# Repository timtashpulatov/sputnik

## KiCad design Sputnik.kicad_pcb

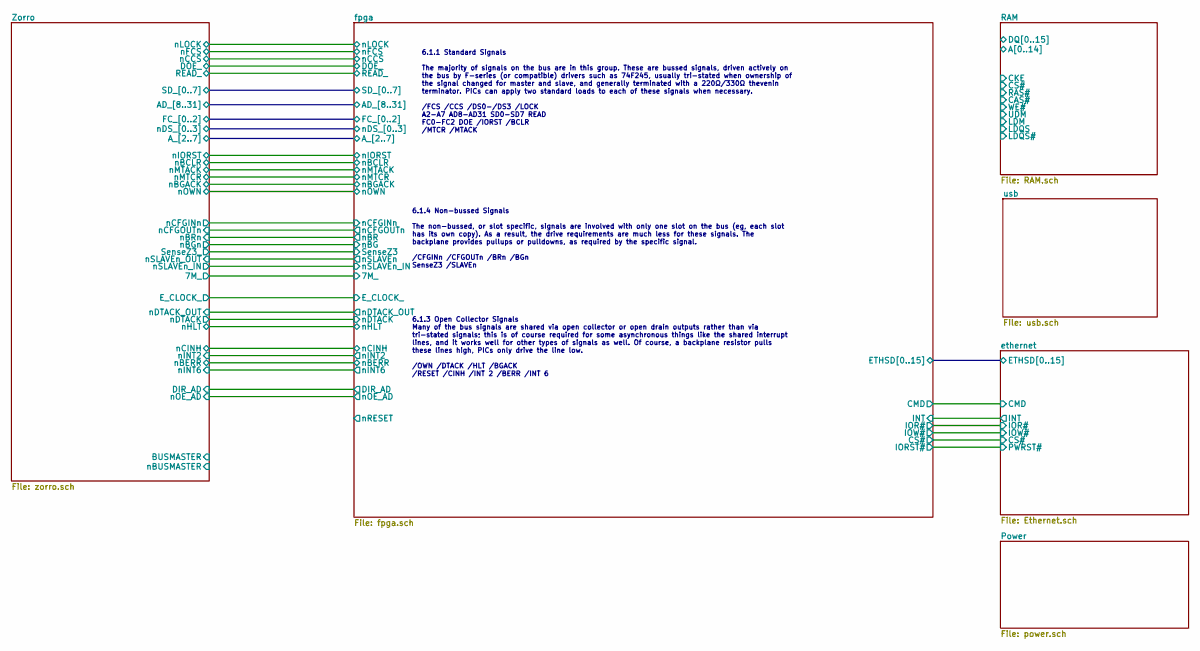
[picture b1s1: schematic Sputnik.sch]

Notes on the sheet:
6.1.1 Standard Signals The majority of signals on the bus are in this group. These are bussed signals, driven actively on the bus by F-series (or compatible) drivers such as 74F245, usually tri-stated when ownership of the signal changed for master and slave, and generally terminated with a 220Ω/33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
6.1.4 Non-bussed Signals The non-bussed, or slot specific, signals are involved with only one slot on the bus (eg, each slot has its own copy). As a result, the drive requirements are much less for these signals. The backplane provides pullups or pulldowns, as required by the specific signal. /CFGI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
6.1.3 Open Collector Signals Many of the bus signals are shared via open collector or open drain outputs rather than via tri-stated signals; this is of course required for some asynchronous things like the shared interrupt lines, and it works well for other types of signals as well. Of course, a ba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

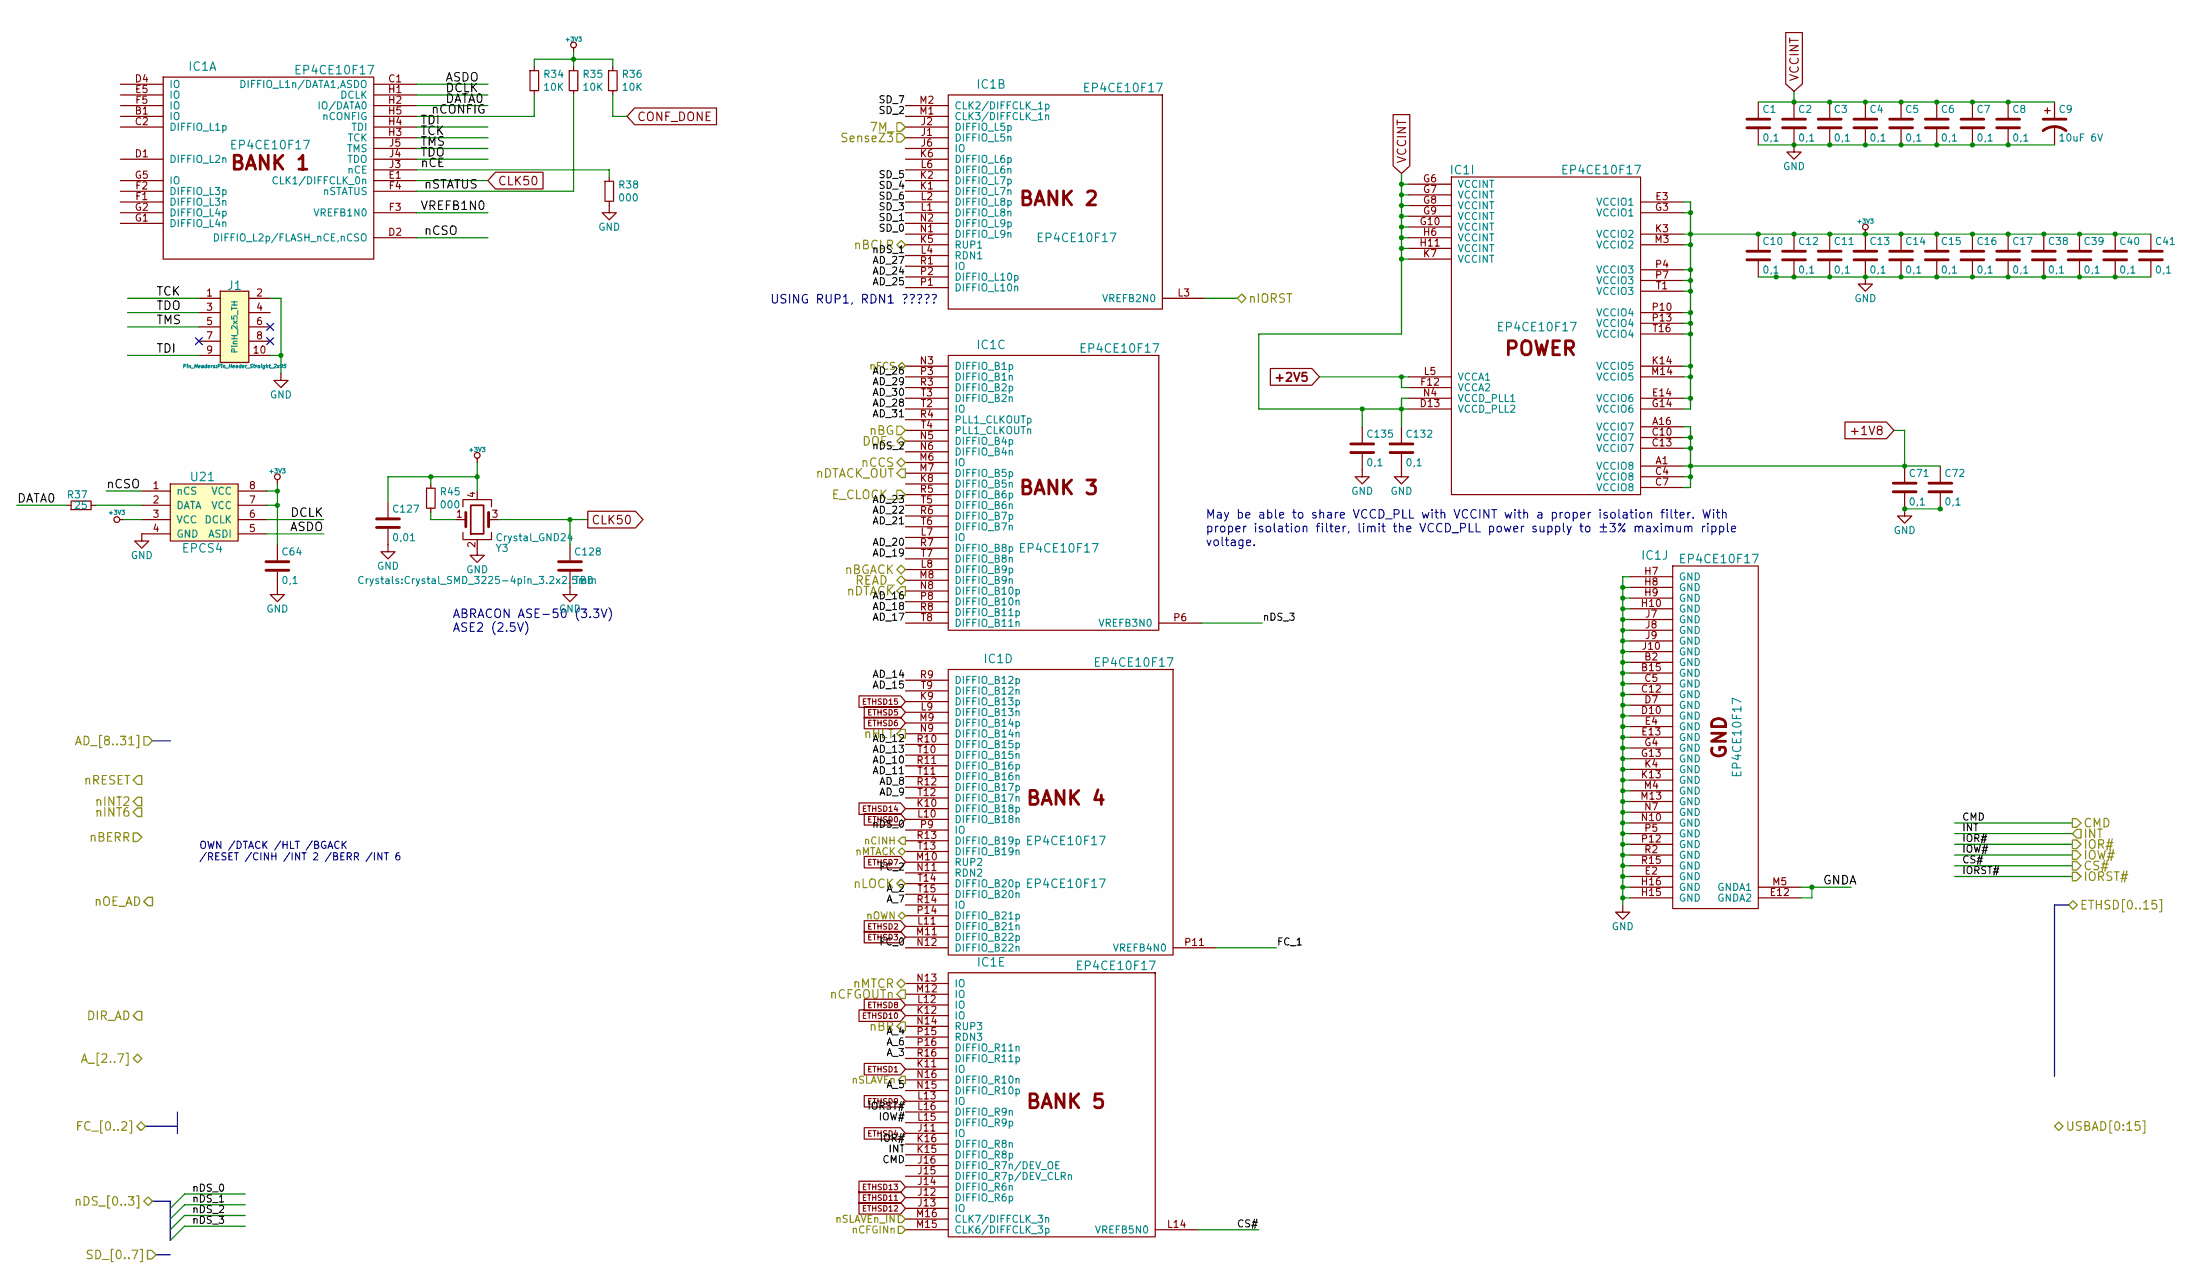
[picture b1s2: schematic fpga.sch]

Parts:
C1, C2, C3, C4, C5, C6, C7, C8, C10, C11, C12, C13, C14, C15, C16, C17, C38, C39, C40, C41, C64, C71, C72: 0,1; C_0603
C9: 10uF 6V
C127: 0,01; C_0603
C128: TBD; C_0603
C132, C135: 0,1; C_0402
IC1: EP4CE10F17; BGA-256-NSMD
J1: Pinheader_2x5_TH_WALL; Pin_Header_Straight_2x05; Manufacturer Part Number SBH11-PBPC-D05-ST-BK
R34, R35, R36: 10K; R_0603
R37: 25; R_0603
R38, R45: 000; R_0603
U21: EPCS4; SOIC-8_3.9x4.9mm_Pitch1.27mm
Y3: Crystal_GND24; Crystal_SMD_3225-4pin_3.2x2.5mm

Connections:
+1V8: C71.1, C72.1, IC1.A1 (VCCIO8), IC1.A16 (VCCIO7), IC1.C4 (VCCIO8), IC1.C7 (VCCIO8), IC1.C10 (VCCIO7), IC1.C13 (VCCIO7); also elsewhere on the board
+2V5: IC1.F12 (VCCA2), IC1.L5 (VCCA1); also elsewhere on the board
+3V3: C10.1, C11.1, C12.1, C13.1, C14.1, C15.1, C16.1, C17.1, C38.1, C39.1, C40.1, C41.1, C64.1, C127.1, IC1.E3 (VCCIO1), IC1.E14 (VCCIO6), IC1.G3 (VCCIO1), IC1.G14 (VCCIO6), IC1.K3 (VCCIO2), IC1.K14 (VCCIO5), IC1.M3 (VCCIO2), IC1.M14 (VCCIO5), IC1.P4 (VCCIO3), IC1.P7 (VCCIO3), IC1.P10 (VCCIO4), IC1.P13 (VCCIO4), IC1.T1 (VCCIO3), IC1.T16 (VCCIO4), R34.1, R35.1, R36.1, R45.1, U21.3 (VCC), U21.7 (VCC), U21.8 (VCC), Y3.4; also elsewhere on the board
/Zorro/7M_: IC1.J2 (DIFFIO_L5p); also elsewhere on the board
/Zorro/AD_8: IC1.R12 (DIFFIO_B17p); also elsewhere on the board
/Zorro/AD_9: IC1.T12 (DIFFIO_B17n); also elsewhere on the board
/Zorro/AD_10: IC1.R11 (DIFFIO_B16p); also elsewhere on the board
/Zorro/AD_11: IC1.T11 (DIFFIO_B16n); also elsewhere on the board
/Zorro/AD_12: IC1.R10 (DIFFIO_B15p); also elsewhere on the board
/Zorro/AD_13: IC1.T10 (DIFFIO_B15n); also elsewhere on the board
/Zorro/AD_14: IC1.R9 (DIFFIO_B12p); also elsewhere on the board
/Zorro/AD_15: IC1.T9 (DIFFIO_B12n); also elsewhere on the board
/Zorro/AD_16: IC1.P8 (DIFFIO_B10n); also elsewhere on the board
/Zorro/AD_17: IC1.T8 (DIFFIO_B11n); also elsewhere on the board
/Zorro/AD_18: IC1.R8 (DIFFIO_B11p); also elsewhere on the board
/Zorro/AD_19: IC1.T7 (DIFFIO_B8n); also elsewhere on the board
/Zorro/AD_20: IC1.R7 (DIFFIO_B8p); also elsewhere on the board
/Zorro/AD_21: IC1.T6 (DIFFIO_B7n); also elsewhere on the board
/Zorro/AD_22: IC1.R6 (DIFFIO_B7p); also elsewhere on the board
/Zorro/AD_23: IC1.T5 (DIFFIO_B6n); also elsewhere on the board
/Zorro/AD_24: IC1.P2 (DIFFIO_L10p); also elsewhere on the board
/Zorro/AD_25: IC1.P1 (DIFFIO_L10n); also elsewhere on the board
/Zorro/AD_26: IC1.P3 (DIFFIO_B1n); also elsewhere on the board
/Zorro/AD_27: IC1.R1 (IO); also elsewhere on the board
/Zorro/AD_28: IC1.T2 (IO); also elsewhere on the board
/Zorro/AD_29: IC1.R3 (DIFFIO_B2p); also elsewhere on the board
/Zorro/AD_30: IC1.T3 (DIFFIO_B2n); also elsewhere on the board
/Zorro/AD_31: IC1.R4 (PLL1_CLKOUTp); also elsewhere on the board
/Zorro/A_2: IC1.T15 (DIFFIO_B20n); also elsewhere on the board
/Zorro/A_3: IC1.R16 (DIFFIO_R11p); also elsewhere on the board
/Zorro/A_4: IC1.P15 (RDN3); also elsewhere on the board
/Zorro/A_5: IC1.N15 (DIFFIO_R10p); also elsewhere on the board
/Zorro/A_6: IC1.P16 (DIFFIO_R11n); also elsewhere on the board
/Zorro/A_7: IC1.R14 (IO); also elsewhere on the board
/Zorro/DOE_: IC1.N5 (DIFFIO_B4p); also elsewhere on the board
/Zorro/E_CLOCK_: IC1.R5 (DIFFIO_B6p); also elsewhere on the board
/Zorro/FC_0: IC1.N12 (DIFFIO_B22n); also elsewhere on the board
/Zorro/FC_1: IC1.P11 (VREFB4N0); also elsewhere on the board
/Zorro/FC_2: IC1.N11 (RDN2); also elsewhere on the board
/Zorro/READ_: IC1.M8 (DIFFIO_B9n); also elsewhere on the board
/Zorro/SD_0: IC1.N1 (DIFFIO_L9n); also elsewhere on the board
/Zorro/SD_1: IC1.N2 (DIFFIO_L9p); also elsewhere on the board
/Zorro/SD_2: IC1.M1 (CLK3/DIFFCLK_1n); also elsewhere on the board
/Zorro/SD_3: IC1.L1 (DIFFIO_L8n); also elsewhere on the board
/Zorro/SD_4: IC1.K1 (DIFFIO_L7n); also elsewhere on the board
/Zorro/SD_5: IC1.K2 (DIFFIO_L7p); also elsewhere on the board
/Zorro/SD_6: IC1.L2 (DIFFIO_L8p); also elsewhere on the board
/Zorro/SD_7: IC1.M2 (CLK2/DIFFCLK_1p); also elsewhere on the board
/Zorro/nBCLR: IC1.K5 (RUP1); also elsewhere on the board
/Zorro/nBGACK: IC1.L8 (DIFFIO_B9p); also elsewhere on the board
/Zorro/nCCS: IC1.M6 (IO); also elsewhere on the board
/Zorro/nCFGINn: IC1.M15 (CLK6/DIFFCLK_3p); also elsewhere on the board
/Zorro/nCFGOUTn: IC1.M12 (IO); also elsewhere on the board
/Zorro/nCINH: IC1.R13 (DIFFIO_B19p); also elsewhere on the board
/Zorro/nDS_0: IC1.P9 (IO); also elsewhere on the board
/Zorro/nDS_1: IC1.L4 (RDN1); also elsewhere on the board
/Zorro/nDS_2: IC1.N6 (DIFFIO_B4n); also elsewhere on the board
/Zorro/nDS_3: IC1.P6 (VREFB3N0); also elsewhere on the board
/Zorro/nDTACK: IC1.N8 (DIFFIO_B10p); also elsewhere on the board
/Zorro/nDTACK_OUT: IC1.M7 (DIFFIO_B5p); also elsewhere on the board
/Zorro/nFCS: IC1.N3 (DIFFIO_B1p); also elsewhere on the board
/Zorro/nHLT: IC1.N9 (DIFFIO_B14n); also elsewhere on the board
/Zorro/nIORST: IC1.L3 (VREFB2N0); also elsewhere on the board
/Zorro/nLOCK: IC1.T14 (DIFFIO_B20p); also elsewhere on the board
/Zorro/nMTACK: IC1.T13 (DIFFIO_B19n); also elsewhere on the board
/Zorro/nMTCR: IC1.N13 (IO); also elsewhere on the board
/Zorro/nOWN: IC1.P14 (DIFFIO_B21p); also elsewhere on the board
/Zorro/nSLAVEn_IN: IC1.M16 (CLK7/DIFFCLK_3n); also elsewhere on the board
/ethernet/CMD: IC1.J16 (DIFFIO_R7n/DEV_OE); also elsewhere on the board
/ethernet/CS#: IC1.L14 (VREFB5N0); also elsewhere on the board
/ethernet/INT: IC1.K15 (DIFFIO_R8p); also elsewhere on the board
/ethernet/IOR#: IC1.K16 (DIFFIO_R8n); also elsewhere on the board
/ethernet/IOW#: IC1.L15 (DIFFIO_R9p); also elsewhere on the board
/fpga/ASDO: IC1.C1 (DIFFIO_L1n/DATA1,ASDO), U21.5 (ASDI)
/fpga/DATA0: IC1.H2 (IO/DATA0), R37.1
/fpga/DCLK: IC1.H1 (DCLK), U21.6 (DCLK)
/fpga/IORST#: IC1.L16 (DIFFIO_R9n); also elsewhere on the board
/fpga/SenseZ3: IC1.J1 (DIFFIO_L5n); also elsewhere on the board
/fpga/TCK: IC1.H3 (TCK), J1.1
/fpga/TDI: IC1.H4 (TDI), J1.9
/fpga/TDO: IC1.J4 (TDO), J1.3
/fpga/TMS: IC1.J5 (TMS), J1.5
/fpga/VREFB1N0: IC1.F3 (VREFB1N0)
/fpga/nBG: IC1.T4 (PLL1_CLKOUTn); also elsewhere on the board
/fpga/nBR: IC1.N14 (RUP3); also elsewhere on the board
/fpga/nCE: IC1.J3 (nCE), R38.1
/fpga/nCONFIG: IC1.H5 (nCONFIG), R34.2
/fpga/nCSO: IC1.D2 (DIFFIO_L2p/FLASH_nCE,nCSO), U21.1 (nCS)
/fpga/nSLAVEn: IC1.N16 (DIFFIO_R10n); also elsewhere on the board
/fpga/nSTATUS: IC1.F4 (nSTATUS), R35.2
CLK50: C128.1, IC1.E1 (CLK1/DIFFCLK_0n), Y3.3
CONF_DONE: R36.2; also elsewhere on the board
ETHSD0: IC1.L10 (DIFFIO_B18n); also elsewhere on the board
ETHSD1: IC1.K11 (IO); also elsewhere on the board
ETHSD2: IC1.L11 (DIFFIO_B21n); also elsewhere on the board
ETHSD3: IC1.M11 (DIFFIO_B22p); also elsewhere on the board
ETHSD4: IC1.J11 (IO); also elsewhere on the board
ETHSD5: IC1.L9 (DIFFIO_B13n); also elsewhere on the board
ETHSD6: IC1.M9 (DIFFIO_B14p); also elsewhere on the board
ETHSD7: IC1.M10 (RUP2); also elsewhere on the board
ETHSD8: IC1.L12 (IO); also elsewhere on the board
ETHSD9: IC1.L13 (IO); also elsewhere on the board
ETHSD10: IC1.K12 (IO); also elsewhere on the board
ETHSD11: IC1.J12 (DIFFIO_R6p); also elsewhere on the board
ETHSD12: IC1.J13 (IO); also elsewhere on the board
ETHSD13: IC1.J14 (DIFFIO_R6n); also elsewhere on the board
ETHSD14: IC1.K10 (DIFFIO_B18p); also elsewhere on the board
ETHSD15: IC1.K9 (DIFFIO_B13p); also elsewhere on the board
GND: C1.2, C2.2, C3.2, C4.2, C5.2, C6.2, C7.2, C8.2, C9.2, C10.2, C11.2, C12.2, C13.2, C14.2, C15.2, C16.2, C17.2, C38.2, C39.2, C40.2, C41.2, C64.2, C71.2, C72.2, C127.2, C128.2, C132.2, C135.2, IC1.B2 (GND), IC1.B15 (GND), IC1.C5 (GND), IC1.C12 (GND), IC1.D7 (GND), IC1.D10 (GND), IC1.E2 (GND), IC1.E4 (GND), IC1.E12 (GNDA2), IC1.E13 (GND), IC1.G4 (GND), IC1.G13 (GND), IC1.H7 (GND), IC1.H8 (GND), IC1.H9 (GND), IC1.H10 (GND), IC1.H15 (GND), IC1.H16 (GND), IC1.J7 (GND), IC1.J8 (GND), IC1.J9 (GND), IC1.J10 (GND), IC1.K4 (GND), IC1.K13 (GND), IC1.M4 (GND), IC1.M5 (GNDA1), IC1.M13 (GND), IC1.N7 (GND), IC1.N10 (GND), IC1.P5 (GND), IC1.P12 (GND), IC1.R2 (GND), IC1.R15 (GND), J1.2, J1.10, R38.2, U21.4 (GND), Y3.2; also elsewhere on the board
unnamed: R37.2, U21.2 (DATA)
unnamed: R45.2, Y3.1
VCCINT: C1.1, C2.1, C3.1, C4.1, C5.1, C6.1, C7.1, C8.1, C9.1, C132.1, C135.1, IC1.D13 (VCCD_PLL2), IC1.G6 (VCCINT), IC1.G7 (VCCINT), IC1.G8 (VCCINT), IC1.G9 (VCCINT), IC1.G10 (VCCINT), IC1.H6 (VCCINT), IC1.H11 (VCCINT), IC1.K7 (VCCINT), IC1.N4 (VCCD_PLL1); also elsewhere on the board

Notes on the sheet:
OWN /DTACK /HLT /BGACK /RESET /CINH /INT 2 /BERR /INT 6
USING RUP1, RDN1 ?????
ABRACON ASE-50 (3.3V) ASE2 (2.5V)
May be able to share VCCD_PLL with VCCINT with a proper isolation filter. With proper isolation filter, limit the VCCD_PLL power supply to ±3% maximum ripple voltage.

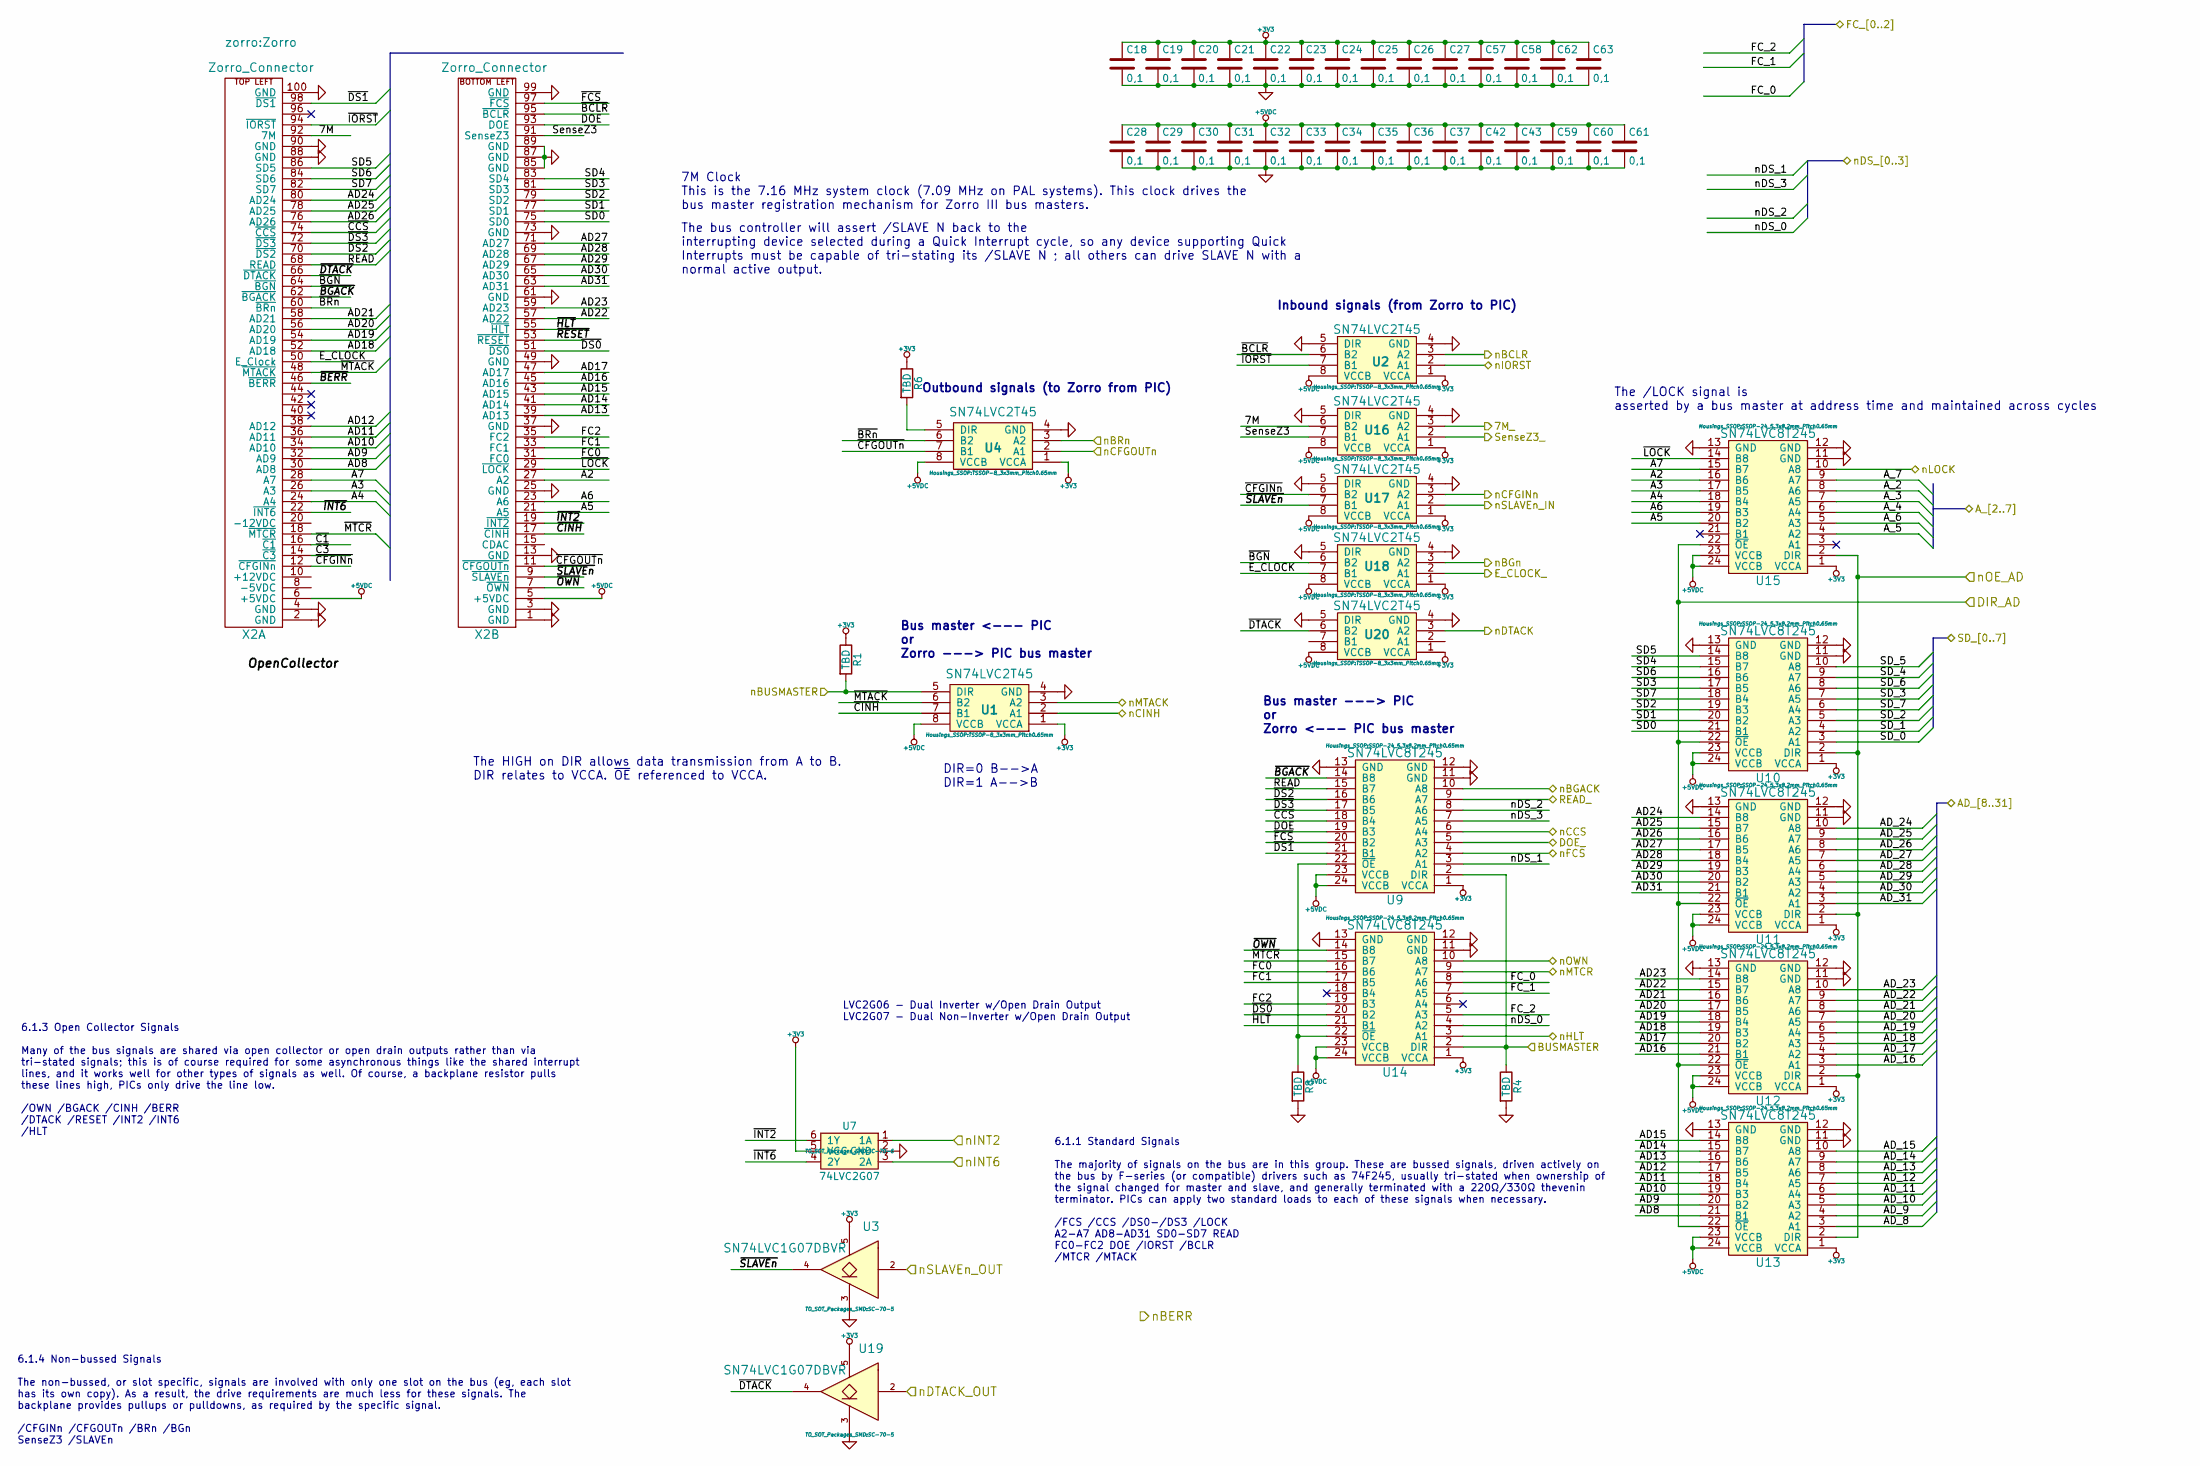
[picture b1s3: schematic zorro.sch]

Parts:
C18, C19, C20, C21, C22, C23, C24, C25, C26, C27, C28, C29, C30, C31, C32, C33, C34, C35, C36, C37, C42, C43, C57, C58, C59, C60, C61, C62, C63: 0,1; C_0603
R1, R4, R6, R8: TBD; R_0603
U1, U2, U4, U16, U17, U18, U20: SN74LVC2T45; TSSOP-8_3x3mm_Pitch0.65mm
U3, U19: SN74LVC1G07DCK; SC-70-5
U7: 74LVC2G07; SC-70-6
U9, U10, U11, U12, U13, U14, U15: SN74LVC8T245; SSOP-24_5.3x8.2mm_Pitch0.65mm
X2: Zorro_Connector; Zorro

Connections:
+3V3: C18.1, C19.1, C20.1, C21.1, C22.1, C23.1, C24.1, C25.1, C26.1, C27.1, C57.1, C58.1, C62.1, C63.1, R1.1, R6.1, U1.1 (VCCA), U2.1 (VCCA), U3.5, U4.1 (VCCA), U7.5 (VCC), U9.1 (VCCA), U10.1 (VCCA), U11.1 (VCCA), U12.1 (VCCA), U13.1 (VCCA), U14.1 (VCCA), U15.1 (VCCA), U16.1 (VCCA), U17.1 (VCCA), U18.1 (VCCA), U19.5, U20.1 (VCCA); also elsewhere on the board
+5VDC: C28.1, C29.1, C30.1, C31.1, C32.1, C33.1, C34.1, C35.1, C36.1, C37.1, C42.1, C43.1, C59.1, C60.1, C61.1, U1.8 (VCCB), U2.8 (VCCB), U4.8 (VCCB), U9.23 (VCCB), U9.24 (VCCB), U10.23 (VCCB), U10.24 (VCCB), U11.23 (VCCB), U11.24 (VCCB), U12.23 (VCCB), U12.24 (VCCB), U13.23 (VCCB), U13.24 (VCCB), U14.23 (VCCB), U14.24 (VCCB), U15.23 (VCCB), U15.24 (VCCB), U16.8 (VCCB), U17.8 (VCCB), U18.8 (VCCB), U20.8 (VCCB), X2.5 (+5VDC), X2.6 (+5VDC); also elsewhere on the board
/Zorro/7M: U16.6 (B2), X2.92 (7M)
/Zorro/7M_: U16.3 (A2); also elsewhere on the board
/Zorro/A2: U15.16 (B6), X2.27 (A2)
/Zorro/A3: U15.17 (B5), X2.26 (A3)
/Zorro/A4: U15.18 (B4), X2.24 (A4)
/Zorro/A5: U15.20 (B2), X2.21 (A5)
/Zorro/A6: U15.19 (B3), X2.23 (A6)
/Zorro/A7: U15.15 (B7), X2.28 (A7)
/Zorro/AD8: U13.21 (B1), X2.30 (AD8)
/Zorro/AD9: U13.20 (B2), X2.32 (AD9)
/Zorro/AD10: U13.19 (B3), X2.34 (AD10)
/Zorro/AD11: U13.18 (B4), X2.36 (AD11)
/Zorro/AD12: U13.17 (B5), X2.38 (AD12)
/Zorro/AD13: U13.16 (B6), X2.39 (AD13)
/Zorro/AD14: U13.15 (B7), X2.41 (AD14)
/Zorro/AD15: U13.14 (B8), X2.43 (AD15)
/Zorro/AD16: U12.21 (B1), X2.45 (AD16)
/Zorro/AD17: U12.20 (B2), X2.47 (AD17)
/Zorro/AD18: U12.19 (B3), X2.52 (AD18)
/Zorro/AD19: U12.18 (B4), X2.54 (AD19)
/Zorro/AD20: U12.17 (B5), X2.56 (AD20)
/Zorro/AD21: U12.16 (B6), X2.58 (AD21)
/Zorro/AD22: U12.15 (B7), X2.57 (AD22)
/Zorro/AD23: U12.14 (B8), X2.59 (AD23)
/Zorro/AD24: U11.14 (B8), X2.80 (AD24)
/Zorro/AD25: U11.15 (B7), X2.78 (AD25)
/Zorro/AD26: U11.16 (B6), X2.76 (AD26)
/Zorro/AD27: U11.17 (B5), X2.71 (AD27)
/Zorro/AD28: U11.18 (B4), X2.69 (AD28)
/Zorro/AD29: U11.19 (B3), X2.67 (AD29)
/Zorro/AD30: U11.20 (B2), X2.65 (AD30)
/Zorro/AD31: U11.21 (B1), X2.63 (AD31)
/Zorro/AD_8: U13.3 (A1); also elsewhere on the board
/Zorro/AD_9: U13.4 (A2); also elsewhere on the board
/Zorro/AD_10: U13.5 (A3); also elsewhere on the board
/Zorro/AD_11: U13.6 (A4); also elsewhere on the board
/Zorro/AD_12: U13.7 (A5); also elsewhere on the board
/Zorro/AD_13: U13.8 (A6); also elsewhere on the board
/Zorro/AD_14: U13.9 (A7); also elsewhere on the board
/Zorro/AD_15: U13.10 (A8); also elsewhere on the board
/Zorro/AD_16: U12.3 (A1); also elsewhere on the board
/Zorro/AD_17: U12.4 (A2); also elsewhere on the board
/Zorro/AD_18: U12.5 (A3); also elsewhere on the board
/Zorro/AD_19: U12.6 (A4); also elsewhere on the board
/Zorro/AD_20: U12.7 (A5); also elsewhere on the board
/Zorro/AD_21: U12.8 (A6); also elsewhere on the board
/Zorro/AD_22: U12.9 (A7); also elsewhere on the board
/Zorro/AD_23: U12.10 (A8); also elsewhere on the board
/Zorro/AD_24: U11.10 (A8); also elsewhere on the board
/Zorro/AD_25: U11.9 (A7); also elsewhere on the board
/Zorro/AD_26: U11.8 (A6); also elsewhere on the board
/Zorro/AD_27: U11.7 (A5); also elsewhere on the board
/Zorro/AD_28: U11.6 (A4); also elsewhere on the board
/Zorro/AD_29: U11.5 (A3); also elsewhere on the board
/Zorro/AD_30: U11.4 (A2); also elsewhere on the board
/Zorro/AD_31: U11.3 (A1); also elsewhere on the board
/Zorro/A_2: U15.8 (A6); also elsewhere on the board
/Zorro/A_3: U15.7 (A5); also elsewhere on the board
/Zorro/A_4: U15.6 (A4); also elsewhere on the board
/Zorro/A_5: U15.4 (A2); also elsewhere on the board
/Zorro/A_6: U15.5 (A3); also elsewhere on the board
/Zorro/A_7: U15.9 (A7); also elsewhere on the board
/Zorro/BUSMASTER: R4.1, U9.2 (DIR), U14.2 (DIR)
/Zorro/DIR_AD: U10.22 (~OE), U11.22 (~OE), U12.22 (~OE), U13.22 (~OE), U15.22 (~OE)
/Zorro/DOE: U9.19 (B3), X2.93 (DOE)
/Zorro/DOE_: U9.5 (A3); also elsewhere on the board
/Zorro/E_CLOCK: U18.7 (B1), X2.50 (E_Clock)
/Zorro/E_CLOCK_: U18.2 (A1); also elsewhere on the board
/Zorro/FC0: U14.16 (B6), X2.31 (FC0)
/Zorro/FC1: U14.17 (B5), X2.33 (FC1)
/Zorro/FC2: U14.19 (B3), X2.35 (FC2)
/Zorro/FC_0: U14.8 (A6); also elsewhere on the board
/Zorro/FC_1: U14.7 (A5); also elsewhere on the board
/Zorro/FC_2: U14.5 (A3); also elsewhere on the board
/Zorro/READ: U9.15 (B7), X2.68 (READ)
/Zorro/READ_: U9.9 (A7); also elsewhere on the board
/Zorro/SD0: U10.21 (B1), X2.75 (SD0)
/Zorro/SD1: U10.20 (B2), X2.77 (SD1)
/Zorro/SD2: U10.19 (B3), X2.79 (SD2)
/Zorro/SD3: U10.17 (B5), X2.81 (SD3)
/Zorro/SD4: U10.15 (B7), X2.83 (SD4)
/Zorro/SD5: U10.14 (B8), X2.86 (SD5)
/Zorro/SD6: U10.16 (B6), X2.84 (SD6)
/Zorro/SD7: U10.18 (B4), X2.82 (SD7)
/Zorro/SD_0: U10.3 (A1); also elsewhere on the board
/Zorro/SD_1: U10.4 (A2); also elsewhere on the board
/Zorro/SD_2: U10.5 (A3); also elsewhere on the board
/Zorro/SD_3: U10.7 (A5); also elsewhere on the board
/Zorro/SD_4: U10.9 (A7); also elsewhere on the board
/Zorro/SD_5: U10.10 (A8); also elsewhere on the board
/Zorro/SD_6: U10.8 (A6); also elsewhere on the board
/Zorro/SD_7: U10.6 (A4); also elsewhere on the board
/Zorro/SenseZ3: U16.7 (B1), X2.91 (SenseZ3)
/Zorro/nBCLR: U2.3 (A2); also elsewhere on the board
/Zorro/nBGACK: U9.10 (A8); also elsewhere on the board
/Zorro/nBUSMASTER: R1.2, U1.5 (DIR)
/Zorro/nCCS: U9.6 (A4); also elsewhere on the board
/Zorro/nCFGINn: U17.3 (A2); also elsewhere on the board
/Zorro/nCFGOUTn: U4.2 (A1); also elsewhere on the board
/Zorro/nCINH: U1.2 (A1); also elsewhere on the board
/Zorro/nDS_0: U14.4 (A2); also elsewhere on the board
/Zorro/nDS_1: U9.3 (A1); also elsewhere on the board
/Zorro/nDS_2: U9.8 (A6); also elsewhere on the board
/Zorro/nDS_3: U9.7 (A5); also elsewhere on the board
/Zorro/nDTACK: U20.3 (A2); also elsewhere on the board
/Zorro/nDTACK_OUT: U19.2; also elsewhere on the board
/Zorro/nFCS: U9.4 (A2); also elsewhere on the board
/Zorro/nHLT: U14.3 (A1); also elsewhere on the board
/Zorro/nINT2: U7.1 (1A)
/Zorro/nINT6: U7.3 (2A)
/Zorro/nIORST: U2.2 (A1); also elsewhere on the board
/Zorro/nLOCK: U15.10 (A8); also elsewhere on the board
/Zorro/nMTACK: U1.3 (A2); also elsewhere on the board
/Zorro/nMTCR: U14.9 (A7); also elsewhere on the board
/Zorro/nOE_AD: U10.2 (DIR), U11.2 (DIR), U12.2 (DIR), U13.2 (DIR), U15.2 (DIR)
/Zorro/nOWN: U14.10 (A8); also elsewhere on the board
/Zorro/nSLAVEn_IN: U17.2 (A1); also elsewhere on the board
/Zorro/~BCLR: U2.6 (B2), X2.95 (~BCLR)
/Zorro/~BERR: X2.46 (~BERR)
/Zorro/~BGACK: U9.14 (B8), X2.62 (~BGACK)
/Zorro/~BGN: U18.6 (B2), X2.64 (~BGN)
/Zorro/~BRn: U4.6 (B2), X2.60 (~BRn)
/Zorro/~C1: X2.16 (~C1)
/Zorro/~C3: X2.14 (~C3)
/Zorro/~CCS: U9.18 (B4), X2.74 (~CCS)
/Zorro/~CFGINn: U17.6 (B2), X2.12 (~CFGINn)
/Zorro/~CFGOUTn: U4.7 (B1), X2.11 (~CFGOUTn)
/Zorro/~CINH: U1.7 (B1), X2.17 (~CINH)
/Zorro/~DS0: U14.20 (B2), X2.51 (~DS0)
/Zorro/~DS1: U9.21 (B1), X2.98 (~DS1)
/Zorro/~DS2: U9.16 (B6), X2.70 (~DS2)
/Zorro/~DS3: U9.17 (B5), X2.72 (~DS3)
/Zorro/~DTACK: U19.4, U20.6 (B2), X2.66 (~DTACK)
/Zorro/~FCS: U9.20 (B2), X2.97 (~FCS)
/Zorro/~HLT: U14.21 (B1), X2.55 (~HLT)
/Zorro/~INT2: U7.6 (1Y), X2.19 (~INT2)
/Zorro/~INT6: U7.4 (2Y), X2.22 (~INT6)
/Zorro/~IORST: U2.7 (B1), X2.94 (~IORST)
/Zorro/~LOCK: U15.14 (B8), X2.29 (~LOCK)
/Zorro/~MTACK: U1.6 (B2), X2.48 (~MTACK)
/Zorro/~MTCR: U14.15 (B7), X2.18 (~MTCR)
/Zorro/~OWN: U14.14 (B8), X2.7 (~OWN)
/Zorro/~RESET: X2.53 (~RESET)
/Zorro/~SLAVEn: U3.4, U17.7 (B1), X2.9 (~SLAVEn)
/fpga/SenseZ3: U16.2 (A1); also elsewhere on the board
/fpga/nBG: U18.3 (A2); also elsewhere on the board
/fpga/nBR: U4.3 (A2); also elsewhere on the board
/fpga/nSLAVEn: U3.2; also elsewhere on the board
GND: C18.2, C19.2, C20.2, C21.2, C22.2, C23.2, C24.2, C25.2, C26.2, C27.2, C28.2, C29.2, C30.2, C31.2, C32.2, C33.2, C34.2, C35.2, C36.2, C37.2, C42.2, C43.2, C57.2, C58.2, C59.2, C60.2, C61.2, C62.2, C63.2, R4.2, R8.2, U1.4 (GND), U2.4 (GND), U2.5 (DIR), U3.3, U4.4 (GND), U7.2 (GND), U9.11 (GND), U9.12 (GND), U9.13 (GND), U10.11 (GND), U10.12 (GND), U10.13 (GND), U11.11 (GND), U11.12 (GND), U11.13 (GND), U12.11 (GND), U12.12 (GND), U12.13 (GND), U13.11 (GND), U13.12 (GND), U13.13 (GND), U14.11 (GND), U14.12 (GND), U14.13 (GND), U15.11 (GND), U15.12 (GND), U15.13 (GND), U16.4 (GND), U16.5 (DIR), U17.4 (GND), U17.5 (DIR), U18.4 (GND), U18.5 (DIR), U19.3, U20.4 (GND), U20.5 (DIR), X2.1 (GND), X2.2 (GND), X2.3 (GND), X2.4 (GND), X2.13 (GND), X2.25 (GND), X2.37 (GND), X2.49 (GND), X2.61 (GND), X2.73 (GND), X2.85 (GND), X2.87 (GND), X2.88 (GND), X2.89 (GND), X2.90 (GND), X2.99 (GND), X2.100 (GND); also elsewhere on the board
unnamed: R6.2, U4.5 (DIR)
unnamed: R8.1, U9.22 (~OE), U14.22 (~OE)

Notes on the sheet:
6.1.3 Open Collector Signals Many of the bus signals are shared via open collector or open drain outputs rather than via tri-stated signals; this is of course required for some asynchronous things like the shared interrupt lines, and it works well for other types of signals as well. Of course, a ba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
6.1.1 Standard Signals The majority of signals on the bus are in this group. These are bussed signals, driven actively on the bus by F-series (or compatible) drivers such as 74F245, usually tri-stated when ownership of the signal changed for master and slave, and generally terminated with a 220Ω/33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
6.1.4 Non-bussed Signals The non-bussed, or slot specific, signals are involved with only one slot on the bus (eg, each slot has its own copy). As a result, the drive requirements are much less for these signals. The backplane provides pullups or pulldowns, as required by the specific signal. /CFGI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
LVC2G06 - Dual Inverter w/Open Drain Output LVC2G07 - Dual Non-Inverter w/Open Drain Output
Inbound signals (from Zorro to PIC)
Bus master ---> PIC or Zorro <--- PIC bus master
Bus master <--- PIC or Zorro ---> PIC bus master
The HIGH on DIR allows data transmission from A to B. DIR relates to VCCA. ~OE~ referenced to VCCA.
Outbound signals (to Zorro from PIC)
The bus controller will assert /SLAVE N back to the interrupting device selected during a Quick Interrupt cycle, so any device supporting Quick Interrupts must be capable of tri-stating its /SLAVE N ; all others can drive SLAVE N with a normal active output.
The /LOCK signal is asserted by a bus master at address time and maintained across cycles
7M Clock This is the 7.16 MHz system clock (7.09 MHz on PAL systems). This clock drives the bus master registration mechanism for Zorro III bus masters.
DIR=0 B-->A DIR=1 A-->B

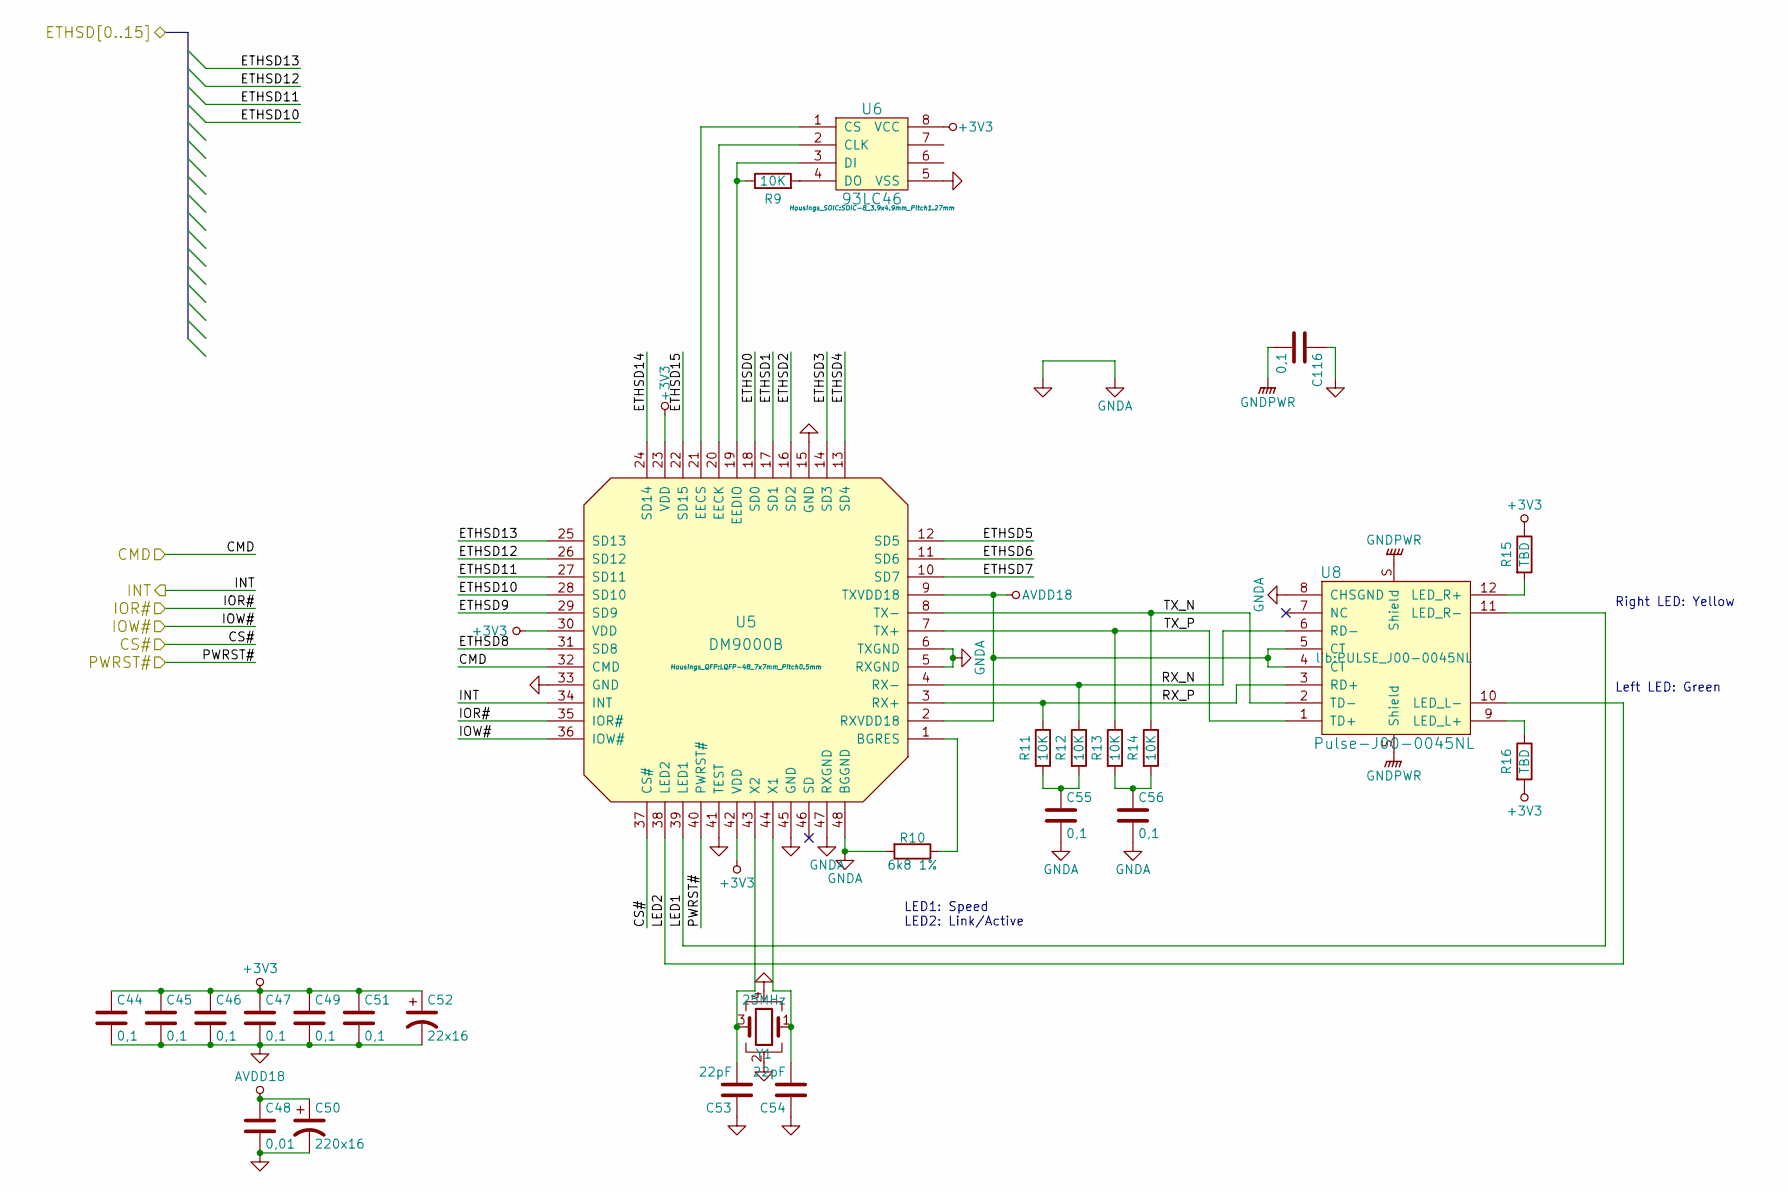
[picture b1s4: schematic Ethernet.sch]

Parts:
C44, C45, C46, C47, C49, C51, C55, C56, C116: 0,1; C_0603
C48: 0,01; C_0603
C50: 220x16; CP_Tantalum_Case-B_EIA-3528-21_Reflow
C52: 22x16
C53, C54: 22pF; C_0603
R9, R11, R12, R13, R14: 10K; R_0603
R10: 6k8 1%; R_0603
R15, R16: TBD; R_0603
U5: DM9000B; LQFP-48_7x7mm_Pitch0.5mm
U6: 93LC46; SOIC-8_3.9x4.9mm_Pitch1.27mm
U8: Pulse-J00-0045NL; PULSE_J00-0045NL
Y1: 25MHz; Crystal_SMD_3225-4pin_3.2x2.5mm

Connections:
+3V3: C44.1, C45.1, C46.1, C47.1, C49.1, C51.1, C52.1, R15.1, R16.2, U5.23 (VDD), U5.30 (VDD), U5.42 (VDD), U6.8 (VCC); also elsewhere on the board
/ethernet/CMD: U5.32 (CMD); also elsewhere on the board
/ethernet/CS#: U5.37 (CS#); also elsewhere on the board
/ethernet/INT: U5.34 (INT); also elsewhere on the board
/ethernet/IOR#: U5.35 (IOR#); also elsewhere on the board
/ethernet/IOW#: U5.36 (IOW#); also elsewhere on the board
/ethernet/LED1: U5.39 (LED1), U8.11 (LED_R-)
/ethernet/LED2: U5.38 (LED2), U8.10 (LED_L-)
/ethernet/RX_N: R12.1, U5.4 (RX-), U8.6 (RD-)
/ethernet/RX_P: R11.1, U5.3 (RX+), U8.3 (RD+)
/ethernet/TX_N: R14.1, U5.8 (TX-), U8.2 (TD-)
/ethernet/TX_P: R13.1, U5.7 (TX+), U8.1 (TD+)
/fpga/IORST#: U5.40 (PWRST#); also elsewhere on the board
AVDD18: C48.1, C50.1, U5.2 (RXVDD18), U5.9 (TXVDD18), U8.4 (CT), U8.5 (CT)
ETHSD0: U5.18 (SD0); also elsewhere on the board
ETHSD1: U5.17 (SD1); also elsewhere on the board
ETHSD2: U5.16 (SD2); also elsewhere on the board
ETHSD3: U5.14 (SD3); also elsewhere on the board
ETHSD4: U5.13 (SD4); also elsewhere on the board
ETHSD5: U5.12 (SD5); also elsewhere on the board
ETHSD6: U5.11 (SD6); also elsewhere on the board
ETHSD7: U5.10 (SD7); also elsewhere on the board
ETHSD8: U5.31 (SD8); also elsewhere on the board
ETHSD9: U5.29 (SD9); also elsewhere on the board
ETHSD10: U5.28 (SD10); also elsewhere on the board
ETHSD11: U5.27 (SD11); also elsewhere on the board
ETHSD12: U5.26 (SD12); also elsewhere on the board
ETHSD13: U5.25 (SD13); also elsewhere on the board
ETHSD14: U5.24 (SD14); also elsewhere on the board
ETHSD15: U5.22 (SD15); also elsewhere on the board
GND: C44.2, C45.2, C46.2, C47.2, C48.2, C49.2, C50.2, C51.2, C52.2, C53.1, C54.1, C55.2, C56.2, C116.1, R10.2, U5.5 (RXGND), U5.6 (TXGND), U5.15 (GND), U5.33 (GND), U5.41 (TEST), U5.45 (GND), U5.47 (RXGND), U5.48 (BGGND), U6.5 (VSS), U8.8 (CHSGND), Y1.2, Y1.4; also elsewhere on the board
GNDPWR: C116.2, U8.S (Shield)
unnamed: C53.2, U5.43 (X2), Y1.3
unnamed: C54.2, U5.44 (X1), Y1.1
unnamed: C55.1, R11.2, R12.2
unnamed: C56.1, R13.2, R14.2
unnamed: R9.1, U5.19 (EEDIO), U6.3 (DI)
unnamed: R9.2, U6.4 (DO)
unnamed: R10.1, U5.1 (BGRES)
unnamed: R15.2, U8.12 (LED_R+)
unnamed: R16.1, U8.9 (LED_L+)
unnamed: U5.20 (EECK), U6.2 (CLK)
unnamed: U5.21 (EECS), U6.1 (CS)

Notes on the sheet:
Left LED: Green
Right LED: Yellow
LED1: Speed LED2: Link/Active
